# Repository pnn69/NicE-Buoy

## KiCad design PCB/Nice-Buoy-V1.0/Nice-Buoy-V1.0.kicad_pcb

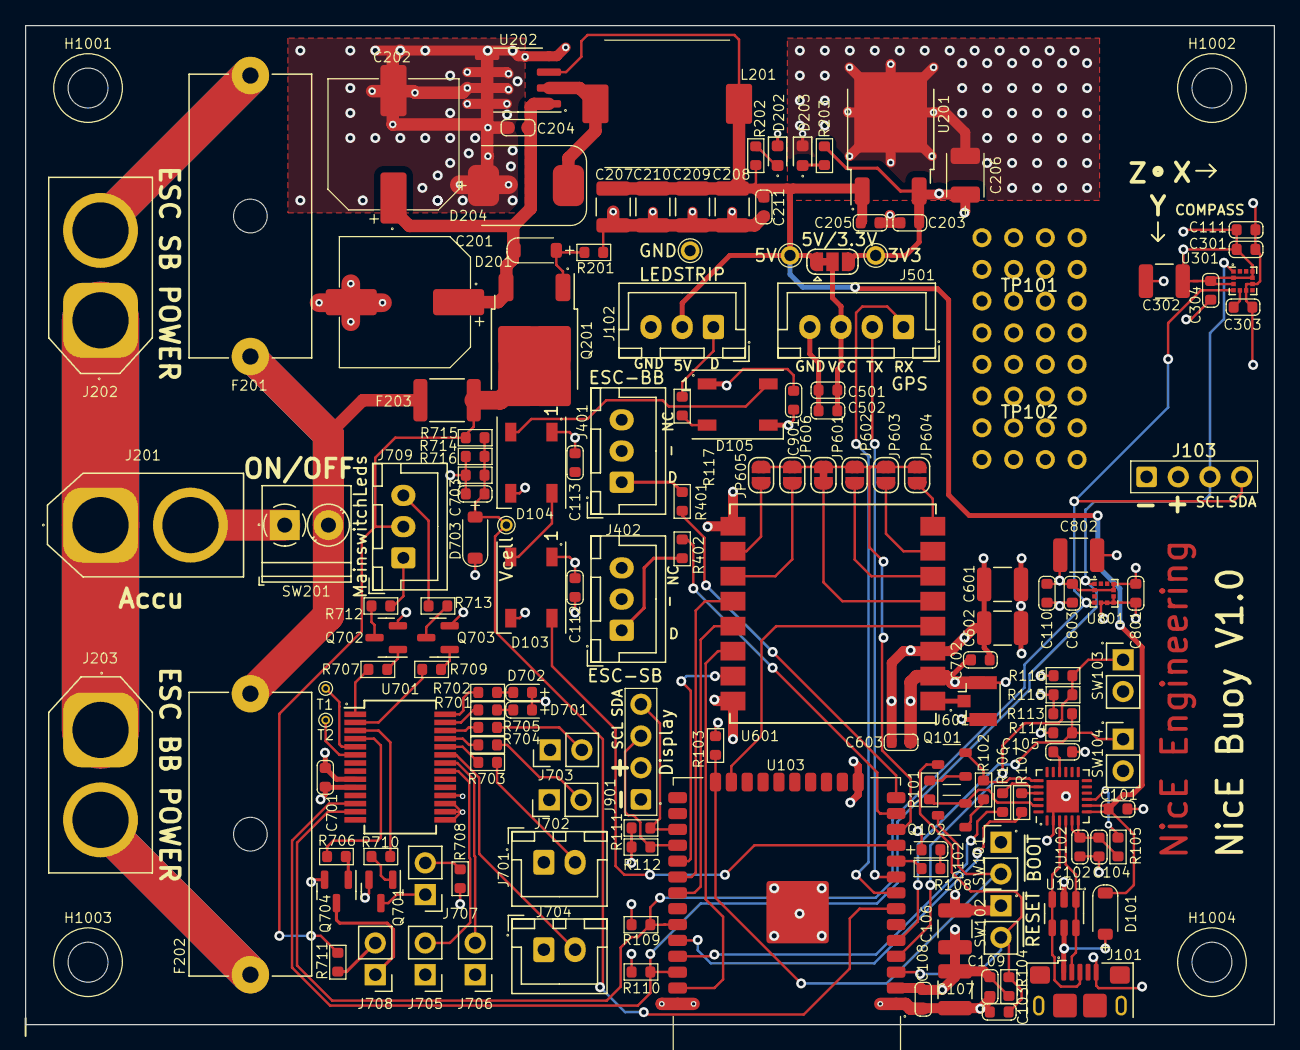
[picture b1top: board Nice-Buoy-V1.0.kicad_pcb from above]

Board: 4 copper layers, 100.0 x 80.0 mm, 154 parts (0 on the bottom side), 95 nets.

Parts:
C101, C102, C105: 4.7u; C_0603
C103, C104, C108, C109, C110, C111, C112, C113, C203, C204, C205, C211, C301, C303, C304, C501, C502, C603, C701, C702, C801, C803, C901: 100n; C_0603
C106, C107, C207, C208, C209, C210, C601, C602: 100u/16V; C_1210_3225Metric
C201, C202: 220u/50V; CP_ALU_D10x10.5
C206: 100u/6.3V; CP_TANT_3.5x2.8x1.9
C302, C802: 10u; C_1210_3225Metric
C703: 1n; C_0603
D101, D201, D703: SM4007PL; D_SOD-123_2.85x1.8x1.3
D102, D701: GREEN; LED_0603
D103, D104, D105: WS2812B; LED_WS2812B_PLCC4_5.0x5.0mm_P3.2mm
D202: 5V; LED_0603_1608Metric
D203: 3.3V; LED_0603_1608Metric
D204: SS36-E3/57T; D_SMC_7.1x6.2x2.65
D702: RED; LED_0603
F201, F202: 10A/T; Fuseholder_Cylinder-5x20mm_Schurter_0031_8201_Horizontal_Op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
F203: 3AT; Fuse_1812_4532Metric
H1001, H1002, H1003, H1004: MountingHole; NPTH_M3
J101: USB_B_Mini; USB_Micro-B_Amphenol_10118193-0001LF_Horizontal
J102: LEDSTRIP; JST_XH_B3B-XH-A_1x03_P2.50mm_Vertical
J103, J901: Display; Header_1x04_P2.54_Male
J201: Accu; AMASS_XT60-M_1x02_P7.20mm_Vertical
J202: ESC SB POWER; AMASS_XT60-F_1x02_P7.20mm_Vertical
J203: ESC BB POWER; AMASS_XT60-F_1x02_P7.20mm_Vertical
J401: ESC-BB; JST_XH_B3B-XH-A_1x03_P2.50mm_Vertical
J402: ESC-SB; JST_XH_B3B-XH-A_1x03_P2.50mm_Vertical
J501: GPS; JST_XH_B4B-XH-A_1x04_P2.50mm_Vertical
J601: Conn_Coaxial; U.FL_Hirose_U.FL-R-SMT-1_Vertical
J701: LED1; JST_XH_B2B-XH-A_1x02_P2.50mm_Vertical
J702: LED2; PinHeader_1x02_P2.54mm_Vertical
J703: LED3; PinHeader_1x02_P2.54mm_Vertical
J704: SW1; JST_XH_B2B-XH-A_1x02_P2.50mm_Vertical
J705: SW3; PinHeader_1x02_P2.54mm_Vertical
J706: SW2; PinHeader_1x02_P2.54mm_Vertical
J707: 3.3V switch; PinHeader_1x02_P2.54mm_Vertical
J708: Vbatt switch; PinHeader_1x02_P2.54mm_Vertical
J709: MainswitchLeds; JST_XH_B3B-XH-A_1x03_P2.50mm_Vertical
JP501: 5V/3.3V; SolderJumper-3_P1.3mm_Bridged12_RoundedPad1.0x1.5mm
JP601: D0; SolderJumper-2_P1.3mm_Bridged_RoundedPad1.0x1.5mm
JP602: D1; SolderJumper-2_P1.3mm_Open_RoundedPad1.0x1.5mm
JP603: D2; SolderJumper-2_P1.3mm_Open_RoundedPad1.0x1.5mm
JP604: D3; SolderJumper-2_P1.3mm_Open_RoundedPad1.0x1.5mm
JP605: D4; SolderJumper-2_P1.3mm_Open_RoundedPad1.0x1.5mm
JP606: D5; SolderJumper-2_P1.3mm_Open_RoundedPad1.0x1.5mm
L201: 68uH/3A; L_11.5x10.0mm
Q101, Q102: 2N7002; SOT-23_1.4x3_P0.95
Q201: NCE01P30K; TO-252-2
Q701, Q702, Q703, Q704: MMBT5551L; SOT-23
R101, R102, R103, R104, R105, R113, R114, R115, R116: 10K; R_0603
R106, R107: 120E; R_0603
R108, R203, R701, R702, R706, R707, R709, R710, R714, R716: 1k; R_0603
R109, R110, R111, R112: 2.2k; R_0603
R117, R201, R401, R402, R703, R704, R705, R708, R711: 100; R_0603
R202: 1.5k; R_0603
R712, R713: 4.7k; R_0603
R715: 6.2k; R_0603
SW101: ~{BOOT}; PinHeader_1x02_P2.54mm_Vertical
SW102: ~{RESET}; PinHeader_1x02_P2.54mm_Vertical
SW103: SW_SPST; PinHeader_1x02_P2.54mm_Vertical
SW104: SW2; PinHeader_1x02_P2.54mm_Vertical
SW201: ON/OFF; TerminalBlock_Phoenix_PT-1,5-2-3.5-H_1x02_P3.50mm_Horizontal
TP101: RW1; ReworkPins
TP102: RW2; ReworkPins
TP201: GND; Testpoint_0.9x1.5
TP202: 3V3; Testpoint_0.9x1.5
TP203: 5V; Testpoint_0.9x1.5
TP701: Vcell; Testpoint_0.6x1.0
TP702: T1; Testpoint_0.4x0.7
TP703: T2; Testpoint_0.4x0.7
U101: SRV05-4; SOT-23-6
U102: CP2104-F03-GMR; QFN-24-1EP_4x4mm_P0.5mm_EP2.6x2.6mm
U103: ESP32-WROOM-32E_(visible_peripherals); ESP32-WROOM-32
U201: AP7363; TO-252-2
U202: XL1509-5.0E1; SOIC-8_3.9x4.9mm_P1.27mm
U301: LSM303C; LGA-12_2x2mm_P0.5mm
U601: Ai-Thinker-Ra-01; Ai-Thinker-Ra-01-LoRa
U701: MCP23017_SS; SSOP-28_5.3x10.2mm_P0.65mm
U801: LIS2HH12; LGA-12_2x2mm_P0.5mm

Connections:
+3.3V: C106.1, C107.1, C108.1, C109.1, C110.1, C111.1, C112.1, C113.1, C205.1, C206.1, C301.1, C302.1, C304.1, C601.1, C602.1, C603.1, C701.1, C702.1, C801.1, C802.1, C803.1, C901.1, D102.2 (A), D103.1 (VDD), D104.1 (VDD), D105.1 (VDD), D701.2 (A), D702.2 (A), D703.1 (K), J103.2, J901.2, JP501.3 (B), R103.1, R104.1, R109.1, R110.1, R111.1, R112.1, R113.2, R115.2, R203.2, R708.1, TP202.1, U103.2 (VDD), U201.3 (VO), U301.2 (CS_XL), U301.3 (CS_MAG), U301.9 (VDD), U301.10 (VDDIO), U601.3 (VDD), U701.9 (VDD), U701.18 (~RESET), U801.2 (~CS), U801.9 (Vdd), U801.10 (Vdd_IO)
+5V: C101.2, C203.1, C207.1, C208.1, C209.1, C210.1, C211.1, D101.1 (K), J102.2, JP501.1 (A), L201.2, R202.1, TP203.1, U102.7 (REGIN), U102.8 (VBUS), U201.1 (VI), U202.3 (FB)
+28V: F203.2, J709.2, Q201.2 (D), R711.1, R715.1
/Accumonitor/GREEN: J709.1, R712.1
/Accumonitor/RED: J709.3, R713.2
/Accumonitor/Vbatt: C703.1, D703.2 (A), R714.1, R715.2, R716.1, TP701.1, U103.7 (GPIO35)
/CPU/ESC_BB: R401.1, U103.14 (MTDI/MISO/D2/GPIO12)
/CPU/ESC_SB: R402.1, U103.13 (MTMS/SCK/CLK/GPIO14)
/CPU/GPSRX: J501.1, U103.8 (GPIO32)
/CPU/GPSTX: J501.2, U103.9 (GPIO33)
/CPU/LEDS: D103.4 (DIN), U103.11 (GPIO26)
/CPU/RADIO_1: U103.37 (MOSI/GPIO23), U601.14 (MOSI)
/CPU/RADIO_2: U103.31 (MISO/GPIO19), U601.13 (MISO)
/CPU/RADIO_3: U103.30 (SCK/GPIO18), U601.12 (SCK)
/CPU/RADIO_4: U103.29 (CS/GPIO5), U601.15 (~NSS)
/CPU/RADIO_5: U103.23 (MTDO/CS/CMD/GPIO15), U601.4 (~RESET)
/CPU/RADIO_6: JP601.1 (A), JP602.1 (A), JP603.1 (A), JP604.1 (A), JP605.1 (A), JP606.1 (A), U103.12 (GPIO27)
/CPU/SCL: J103.3, R110.2, U103.36 (SCL/GPIO22), U301.1 (SCL/SPC), U701.12 (SCK), U801.1 (SCL/SPC)
/CPU/SCL_DISP: J901.3, R112.2, U103.28 (TXD/GPIO17)
/CPU/SDA: J103.4, R109.2, U103.33 (SDA/GPIO21), U301.4 (SDA/SDI/SDO), U701.13 (SDA), U801.4 (SDA/SDI)
/CPU/SDA_DISP: J901.4, R111.2, U103.27 (RXD/GPIO16)
/GPS/Vext: C501.1, C502.1, J501.3, JP501.2 (C)
/PSU/ACC: J201.2, SW201.1 (A)
/PSU/POWER: F201.2, F202.2, F203.1, SW201.2 (B)
DR0: Q102.3 (C), R103.2, SW101.2, U103.24 (D0/GPIO2)
DTR: Q102.2 (E), R101.2, U102.23 (DTR)
EN: C103.1, Q101.3 (C), R104.2, SW102.2, U103.3 (CHIP_PU/EN)
GND: C101.1, C102.1, C103.2, C104.1, C105.1, C106.2, C107.2, C108.2, C109.2, C110.2, C111.2, C112.2, C113.2, C201.2, C202.2, C203.2, C204.2, C205.2, C206.2, C207.2, C208.2, C209.2, C210.2, C211.2, C301.2, C302.2, C303.2, C304.2, C501.2, C502.2, C601.2, C602.2, C603.2, C701.2, C702.2, C703.2, C801.2, C802.2, C803.2, C901.2, D103.3 (VSS), D104.3 (VSS), D105.3 (VSS), D202.1 (K), D203.1 (K), D204.2 (A), J101.5 (GND), J102.3, J103.1, J201.1, J202.1, J203.1, J401.2, J402.2, J501.4, J601.2 (Ext), J701.1, J702.1, J703.1, J704.1, J705.1, J706.1, J901.1, Q701.2 (E), Q702.2 (E), Q703.2 (E), Q704.2 (E), R114.1, R116.1, R201.1, R714.2, R716.2, SW101.1, SW102.1, SW103.2 (B), SW104.2 (B), TP201.1, U101.2 (VN), U102.2 (GND), U102.25 (GND), U103.1 (GND), U103.15 (GND), U103.38 (GND), U103.39 (GND), U201.2 (GND), U202.4 (~EN), U202.5 (GND), U202.6 (GND), U202.7 (GND), U202.8 (GND), U301.6 (GND), U301.8 (GND), U601.2 (GND), U601.9 (GND), U601.16 (GND), U701.10 (VSS), U701.15 (A0), U701.16 (A1), U701.17 (A2), U801.5 (RES), U801.6 (GND), U801.7 (GND), U801.8 (GND)
LED1: R703.1, U701.24 (GPA3)
LED2: R704.1, U701.25 (GPA4)
LED3: R705.1, U701.26 (GPA5)
unnamed: D101.2 (A), J101.1 (VBUS), U101.5 (VP)
unnamed: D102.1 (K), R108.2
unnamed: D103.2 (DOUT), D104.4 (DIN)
unnamed: D104.2 (DOUT), D105.4 (DIN)
unnamed: D105.2 (DOUT), R117.2
unnamed: D201.2 (A), Q201.1 (G), R201.2
unnamed: C201.1, C202.1, C204.1, D201.1 (K), Q201.3 (S), U202.1 (VIN)
unnamed: D202.2 (A), R202.2
unnamed: D203.2 (A), R203.1
unnamed: D204.1 (K), L201.1, U202.2 (OUT)
unnamed: D701.1 (K), R701.2
unnamed: D702.1 (K), R702.2
unnamed: J101.3 (D+), U101.3 (IO2), U101.4 (IO3), U102.3 (D+)
unnamed: J101.2 (D-), U101.1 (IO1), U101.6 (IO4), U102.4 (D-)
unnamed: J102.1, R117.1
unnamed: F201.1, J202.2
unnamed: F202.1, J203.2
unnamed: J401.1, R401.2
unnamed: J402.1, R402.2
unnamed: J601.1 (In), U601.1 (ANT)
unnamed: J701.2, R703.2
unnamed: J702.2, R704.2
unnamed: J703.2, R705.2
unnamed: J707.1, Q701.3 (C)
unnamed: J707.2, R708.2
unnamed: J708.1, Q704.3 (C)
unnamed: J708.2, R711.2
unnamed: JP601.2 (B), U601.5 (DIO0)
unnamed: JP602.2 (B), U601.6 (DIO1)
unnamed: JP603.2 (B), U601.7 (DIO2)
unnamed: JP604.2 (B), U601.8 (DIO3)
unnamed: JP605.2 (B), U601.10 (DIO4)
unnamed: JP606.2 (B), U601.11 (DIO5)
unnamed: Q101.1 (B), R101.1
unnamed: Q102.1 (B), R102.1
unnamed: Q701.1 (B), R706.2
unnamed: Q702.1 (B), R707.2
unnamed: Q702.3 (C), R712.2
unnamed: Q703.1 (B), R709.2
unnamed: Q703.3 (C), R713.1
unnamed: Q704.1 (B), R710.2
unnamed: R115.1, R116.2, SW103.1 (A), U103.4 (GPIO36)
unnamed: R113.1, R114.2, SW104.1 (A), U103.5 (GPIO39)
unnamed: R106.2, U102.20 (RXD)
unnamed: R107.2, U102.21 (TXD)
unnamed: C102.2, C104.2, R105.1, U102.5 (VIO), U102.6 (VDD)
unnamed: C105.2, U102.16 (VPP)
unnamed: R105.2, U102.9 (~RSTb)
unnamed: R108.1, U103.10 (GPIO25)
unnamed: C303.1, U301.5 (C1)
unnamed: R701.1, U701.27 (GPA6)
unnamed: R702.1, U701.28 (GPA7)
unnamed: R707.1, U701.1 (GPB0)
unnamed: R709.1, U701.2 (GPB1)
unnamed: R706.1, U701.3 (GPB2)
unnamed: R710.1, U701.4 (GPB3)
unnamed: TP702.1, U701.5 (GPB4)
unnamed: TP703.1, U701.6 (GPB5)
RTS: Q101.2 (E), R102.2, U102.19 (RTS)
RX: R107.1, U103.34 (RXD/GPIO3)
SW1: J704.2, U701.23 (GPA2)
SW2: J706.2, U701.22 (GPA1)
SW3: J705.2, U701.21 (GPA0)
TX: R106.1, U103.35 (TXD/GPIO1)

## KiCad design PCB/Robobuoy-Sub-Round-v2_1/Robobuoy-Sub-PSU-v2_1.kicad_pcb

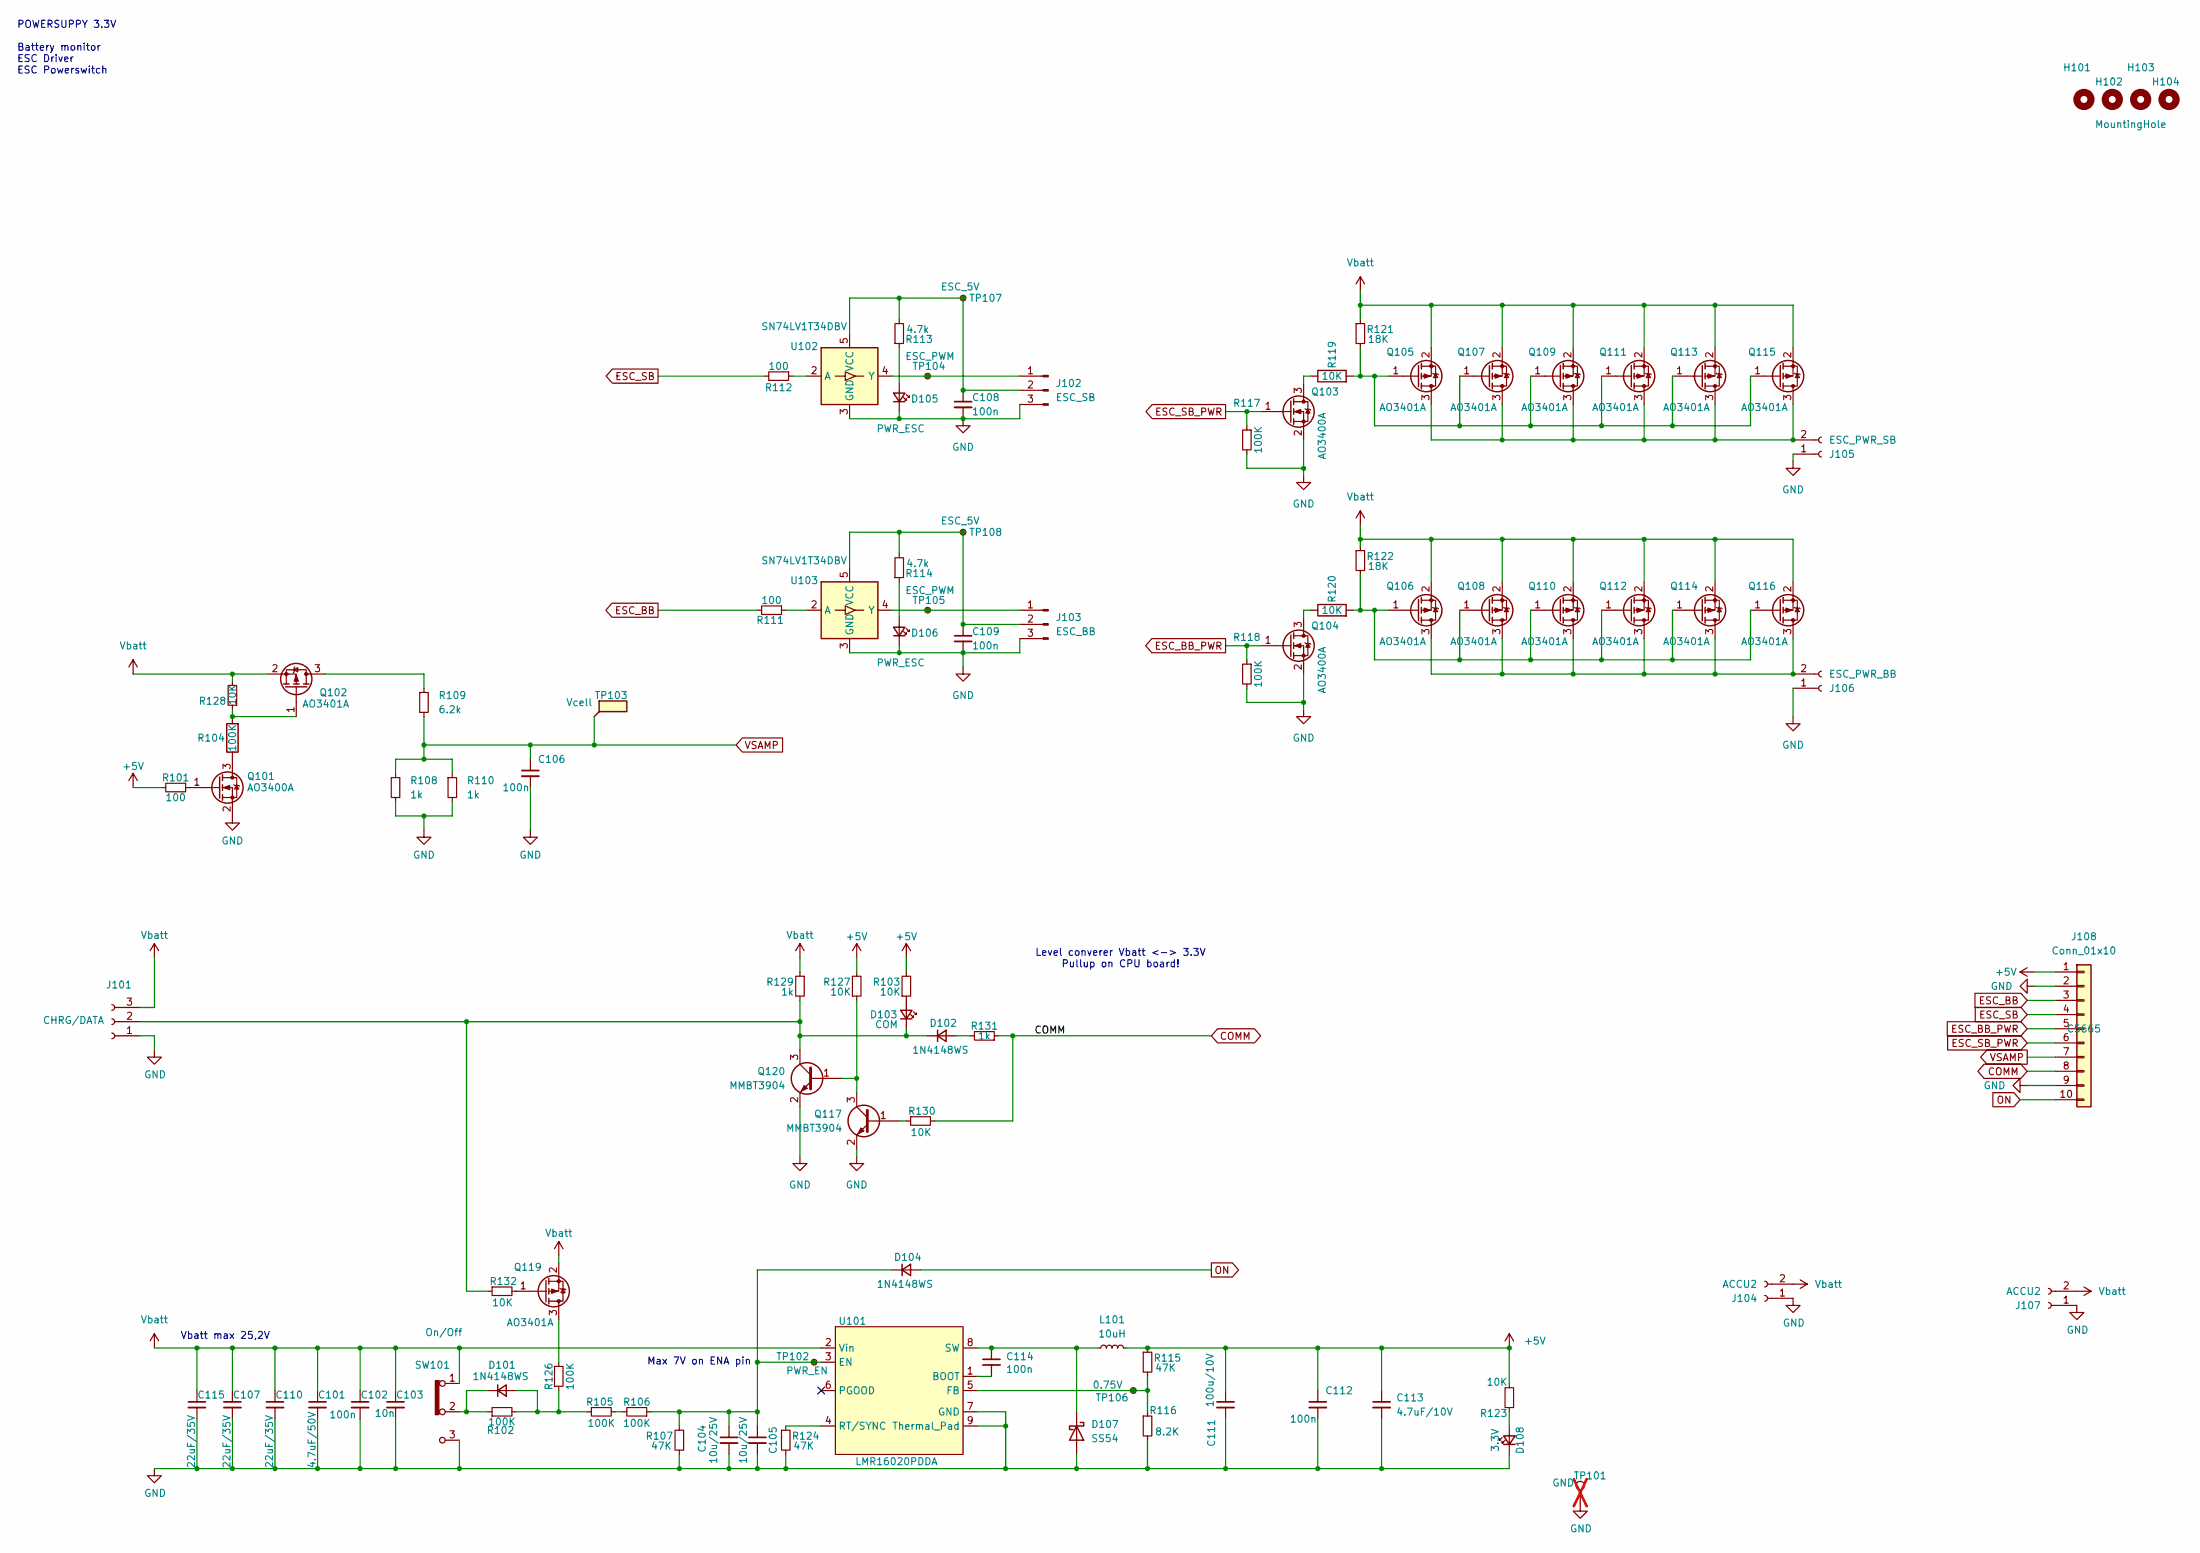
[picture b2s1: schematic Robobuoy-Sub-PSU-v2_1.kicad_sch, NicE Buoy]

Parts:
C101: 4.7uF/50V; C_1206_(1.6); LCSC C29823
C102, C106, C108, C109, C112, C114: 100n; C_0603; LCSC C14663
C103: 10n; C_0603; LCSC C57112
C104, C105: 10u/25V; C_0805; LCSC C15850
C107, C110, C115: 22uF/35V; C_1206_(1.6); LCSC C6119969
C111: 100u/10V; C_1210_3225Metric; LCSC C23742
C113: 4.7uF/10V; C_1206_(1.6); LCSC C29823
D101, D102, D104: 1N4148WS; D_SOD-323_1.8x1.4x1.15; LCSC C2128
D103: COM; LED_0603_1608Metric; LCSC C2286
D105, D106: PWR_ESC; LED_0603_1608Metric; LCSC C2286
D107: SS54; D_SMA; LCSC C22452
D108: 3.3V; LED_0805; LCSC C2297
H101, H102, H103, H104: MountingHole; NPTH_M3
J101: CHRG/DATA; MR60PW-M; LCSC C19268044
J102: ESC_SB; JST_XH_B3B-XH-A_1x03_P2.50mm_Vertical; LCSC C5341202
J103: ESC_BB; JST_XH_B3B-XH-A_1x03_P2.50mm_Vertical; LCSC C5341202
J104, J107: ACCU2; AMASS_XT60IPW-M_1x03_P7.20mm_Horizontal
J105: ESC_PWR_SB; AMASS_XT60PW-F_1x02_P7.20mm_Horizontal; LCSC C428722
J106: ESC_PWR_BB; AMASS_XT60PW-F_1x02_P7.20mm_Horizontal; LCSC C428722
J108: Conn_01x10; IDC-Header_2x05_P2.54mm_Vertical; LCSC C5665
L101: 10uH; L_6.6x7.0mm; LCSC C2894722
Q101, Q103, Q104: AO3400A; SOT-23; LCSC C20917
Q102, Q105, Q106, Q107, Q108, Q109, Q110, Q111, Q112, Q113, Q114, Q115, Q116, Q119: AO3401A; SOT-23; LCSC C15127
Q117, Q120: MMBT3904; SOT-23
R101, R111, R112: 100; R_0603; LCSC C22775
R102, R105, R106, R117, R118, R126: 100K; R_0603; LCSC C25804
R103, R123, R127, R128, R130, R132: 10K; R_0603; LCSC C25804
R104: 100K; R_0603; Farnell 2331736
R107, R115: 47K; R_0603
R108, R110, R129, R131: 1k; R_0603; LCSC C21190
R109: 6.2k; R_0603; LCSC C25804
R113, R114: 4.7k; R_0603; LCSC C4177
R116: 8.2K; R_0603
R119, R120: 10K; R_0603; Farnell 2331736
R121, R122: 18K; R_0603; LCSC C25810
R124: 47K; R_0603; LCSC C25819
SW101: On/Off; Header_1x03_P2.54_Male; LCSC C2937625
TP101: GND; TestPoint_Loop_D2.54mm_Drill1.5mm_Beaded; not fitted
TP102: PWR_EN; Testpad_1
TP103: Vcell; Testpad_1
TP104: ESC_PWM; Testpad_1
TP105: ESC_PWM; Testpad_1.4
TP106: 0.75V; Testpad_1
TP107, TP108: ESC_5V; Testpad_1
U101: LMR16020PDDA; SOIC-8-1EP_3.9x4.9mm_P1.27mm_EP2.41x3.81mm_ThermalVias; LCSC C190006
U102, U103: SN74LV1T34DBV; SOT-23-5; LCSC C100024

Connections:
+5V: C111.1, C112.1, C113.1, J108.1, L101.2, R101.2, R103.2, R115.1, R123.2, R127.2
COMM: J108.8, R130.2, R131.1
ESC_BB: J108.3, R111.2
ESC_BB_PWR: J108.5, Q104.1 (G), R118.1
ESC_SB: J108.4, R112.2
ESC_SB_PWR: J108.6, Q103.1 (G), R117.1
GND: C101.2, C102.2, C103.2, C104.2, C105.2, C106.2, C107.2, C108.2, C109.2, C110.2, C111.2, C112.2, C113.2, C115.2, D105.1 (K), D106.1 (K), D107.2 (A), D108.1 (K), J101.1, J102.3, J103.3, J104.1, J105.1, J106.1, J107.1, J108.2, J108.9, Q101.2 (S), Q103.2 (S), Q104.2 (S), Q117.2 (E), Q120.2 (E), R107.2, R108.2, R110.2, R116.2, R117.2, R118.2, R124.2, SW101.3, TP101.1, U101.7 (GND), U101.9 (Thermal_Pad), U102.3 (GND), U103.3 (GND)
unnamed: D101.2 (A), R102.2, R105.1, R126.1
unnamed: D101.1 (K), R102.1, SW101.2
unnamed: D102.2 (A), R131.2
unnamed: D102.1 (K), D103.1 (K), J101.2, Q120.3 (C), R129.2, R132.1
unnamed: D103.2 (A), R103.1
unnamed: C104.1, C105.1, D104.1 (K), R106.1, R107.1, TP102.1, U101.3 (EN)
unnamed: D105.2 (A), R113.1
unnamed: D106.2 (A), R114.1
unnamed: C114.1, D107.1 (K), L101.1, U101.8 (SW)
unnamed: D108.2 (A), R123.1
unnamed: J102.1, TP104.1, U102.4 (Y)
unnamed: C108.1, J102.2, R113.2, TP107.1, U102.5 (VCC)
unnamed: J103.1, TP105.1, U103.4 (Y)
unnamed: C109.1, J103.2, R114.2, TP108.1, U103.5 (VCC)
unnamed: J105.2, Q105.3 (D), Q107.3 (D), Q109.3 (D), Q111.3 (D), Q113.3 (D), Q115.3 (D)
unnamed: J106.2, Q106.3 (D), Q108.3 (D), Q110.3 (D), Q112.3 (D), Q114.3 (D), Q116.3 (D)
unnamed: Q101.3 (D), R104.1
unnamed: Q101.1 (G), R101.1
unnamed: Q102.3 (D), R109.1
unnamed: Q102.1 (G), R104.2, R128.1
unnamed: Q103.3 (D), R119.1
unnamed: Q104.3 (D), R120.1
unnamed: Q105.1 (G), Q107.1 (G), Q109.1 (G), Q111.1 (G), Q113.1 (G), Q115.1 (G), R119.2, R121.2
unnamed: Q106.1 (G), Q108.1 (G), Q110.1 (G), Q112.1 (G), Q114.1 (G), Q116.1 (G), R120.2, R122.2
unnamed: Q117.1 (B), R130.1
unnamed: Q117.3 (C), Q120.1 (B), R127.1
unnamed: Q119.3 (D), R126.2
unnamed: Q119.1 (G), R132.2
unnamed: R105.2, R106.2
unnamed: C114.2, U101.1 (BOOT)
unnamed: R115.2, R116.1, TP106.1, U101.5 (FB)
unnamed: R124.1, U101.4 (RT/SYNC)
unnamed: R112.1, U102.2 (A)
unnamed: R111.1, U103.2 (A)
ON: D104.2 (A), J108.10
VSAMP: C106.1, J108.7, R108.1, R109.2, R110.1, TP103.1
Vbatt: C101.1, C102.1, C103.1, C107.1, C110.1, C115.1, J101.3, J104.2, J107.2, Q102.2 (S), Q105.2 (S), Q106.2 (S), Q107.2 (S), Q108.2 (S), Q109.2 (S), Q110.2 (S), Q111.2 (S), Q112.2 (S), Q113.2 (S), Q114.2 (S), Q115.2 (S), Q116.2 (S), Q119.2 (S), R121.1, R122.1, R128.2, R129.1, SW101.1, U101.2 (Vin)

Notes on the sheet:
Max 7V on ENA pin
POWERSUPPY 3.3V Battery monitor ESC Driver ESC Powerswitch
Level converer Vbatt <-> 3.3V Pullup on CPU board!
Vbatt max 25,2V

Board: 4 copper layers, 98 parts (0 on the bottom side), 44 nets, no tracks yet.

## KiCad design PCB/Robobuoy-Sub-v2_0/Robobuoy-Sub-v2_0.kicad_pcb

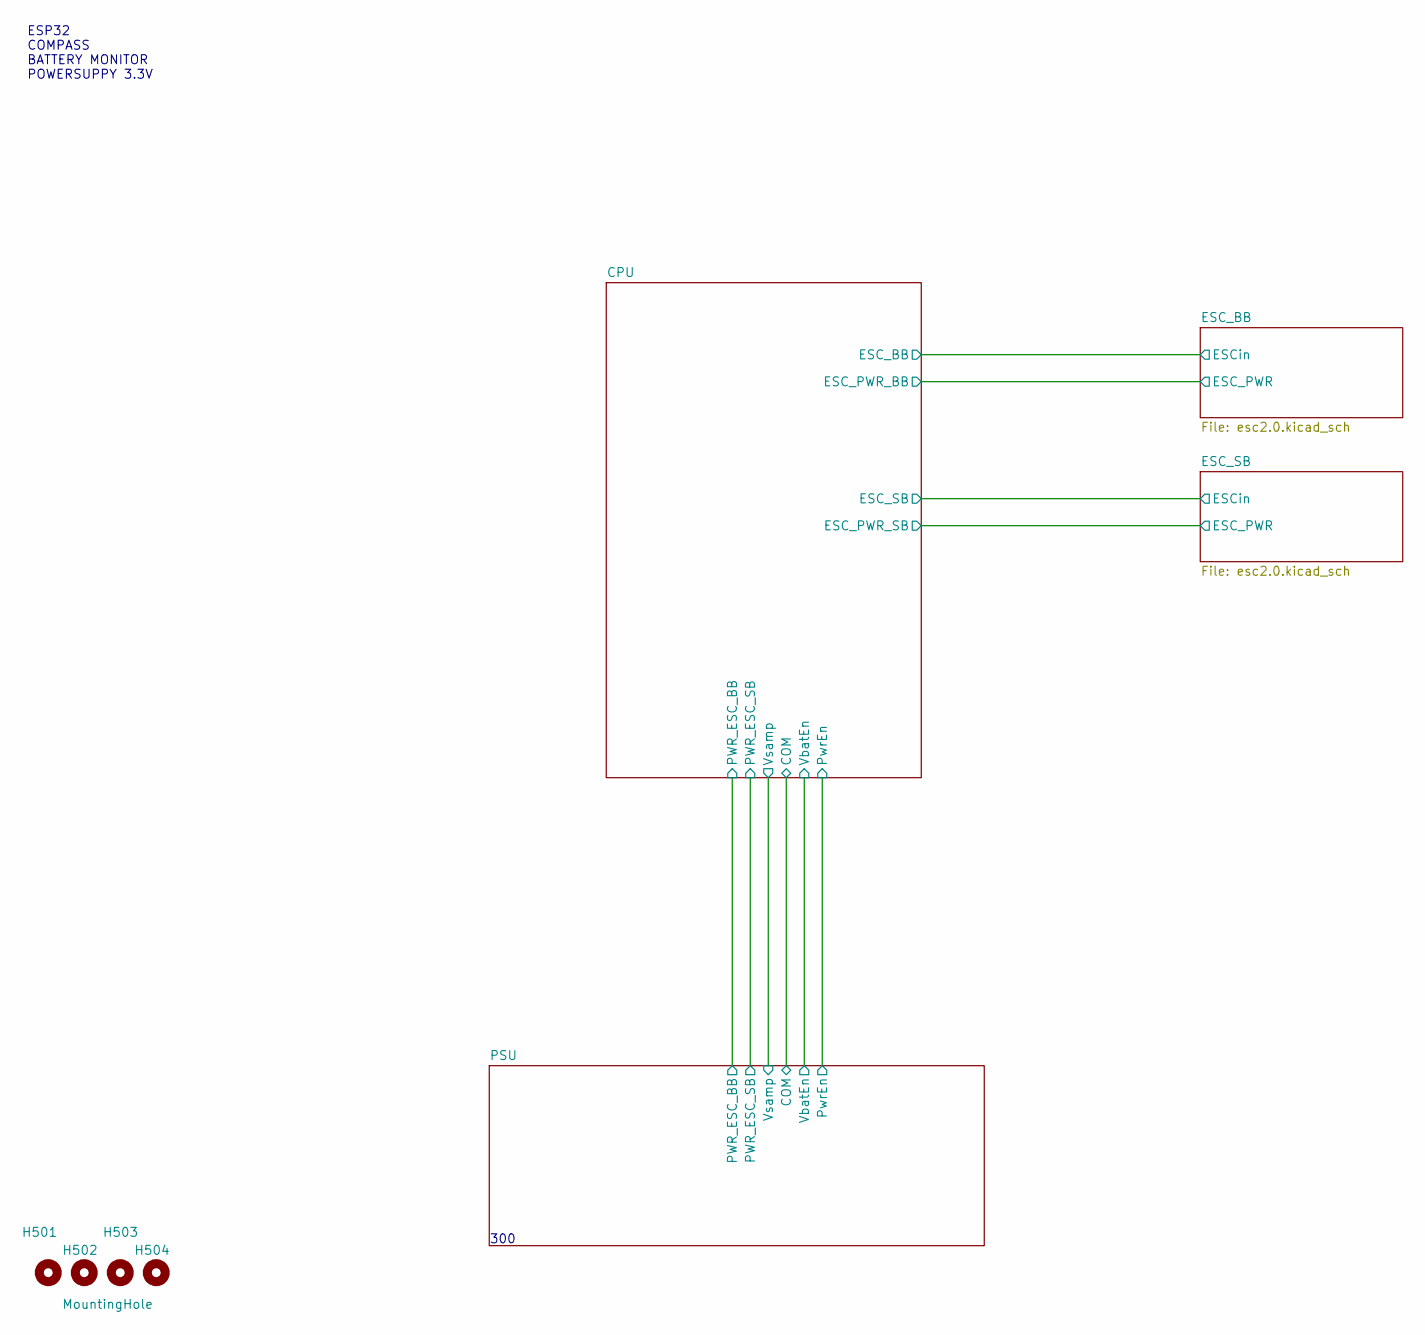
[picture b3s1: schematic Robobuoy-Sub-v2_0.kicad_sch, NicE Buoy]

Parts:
H501, H502, H503, H504: MountingHole; NPTH_M3

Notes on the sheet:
300
ESP32 COMPASS BATTERY MONITOR POWERSUPPY 3.3V

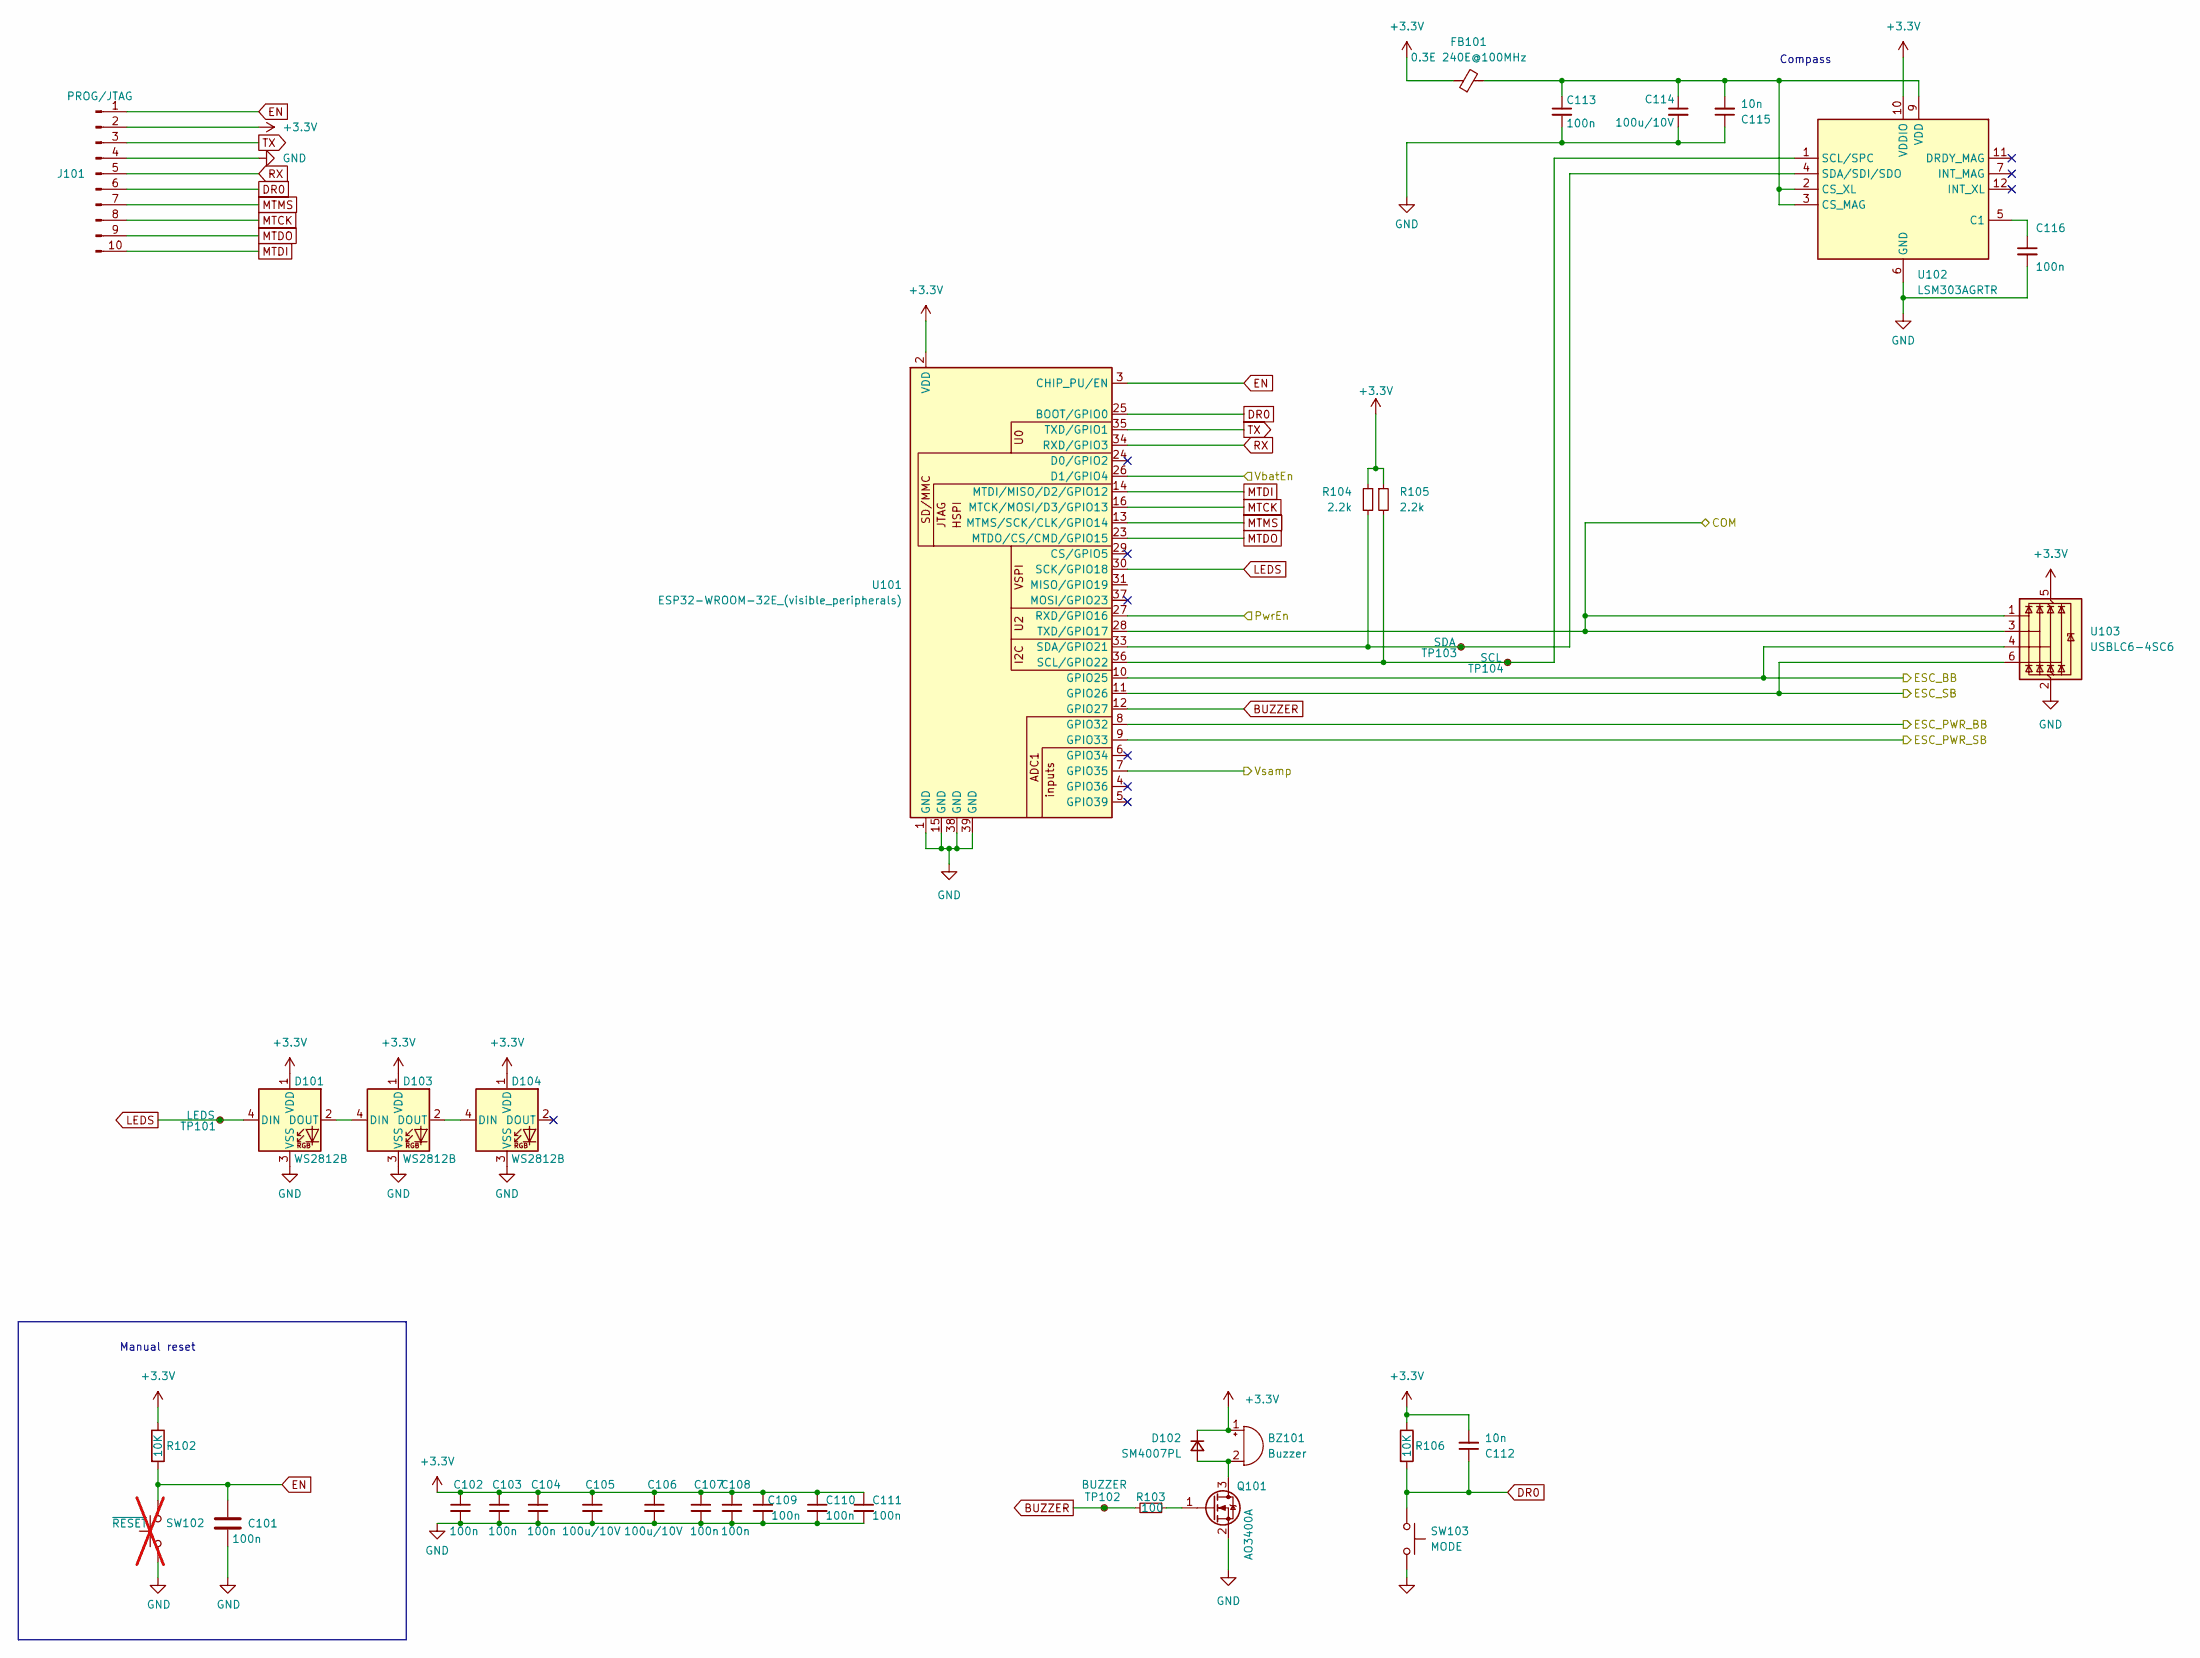
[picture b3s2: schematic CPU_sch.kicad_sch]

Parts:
BZ101: Buzzer; Buzzer-12x6.5x5.2; LCSC C968749
C101, C102, C103, C104, C107, C108, C109, C110, C111, C113, C116: 100n; C_0603; LCSC C14663
C105, C106, C114: 100u/10V; C_1210_3225Metric; LCSC C23742
C112, C115: 10n; C_0603; LCSC C57112
D101, D103, D104: WS2812B; LED_WS2812B_PLCC4_5.0x5.0mm_P3.2mm; LCSC C2843785
D102: SM4007PL; D_SOD-123_2.85x1.8x1.3; LCSC C64898
FB101: 0.3E 240E@100MHz; L_0805_(1.2); LCSC C2941558
J101: PROG/JTAG; IDC-Header_2x05_P2.54mm_Vertical; LCSC C5665
Q101: AO3400A; SOT-23; LCSC C20917
R102, R106: 10K; R_0603; Farnell 2331736
R103: 100; R_0603; LCSC C22775
R104, R105: 2.2k; R_0603; LCSC C4190
SW102: ~{RESET}; PinHeader_1x02_P2.54mm_Vertical; not fitted
SW103: MODE; SW_SPST_TL3342; LCSC C318884
TP101: LEDS; Testpad_1
TP102: BUZZER; Testpad_1
TP103: SDA; Testpad_1
TP104: SCL; Testpad_1
U101: ESP32-WROOM-32E_(visible_peripherals); ESP32-WROOM-32; LCSC C82899
U102: LSM303AGRTR; LGA-12_2x2mm_P0.5mm; LCSC C126671
U103: USBLC6-4SC6; SOT-23-6; LCSC C5197386

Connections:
+3.3V: BZ101.1 (+), C102.1, C103.1, C104.1, C105.1, C106.1, C107.1, C108.1, C109.1, C110.1, C111.1, C112.2, D101.1 (VDD), D102.1 (K), D103.1 (VDD), D104.1 (VDD), FB101.1, J101.2, R102.1, R104.1, R105.1, R106.1, U101.2 (VDD), U102.10 (VDDIO), U103.5 (VBUS); also elsewhere on the board
/CPU/COM: U101.28 (TXD/GPIO17), U103.1 (I/O1), U103.3 (I/O2); also elsewhere on the board
/CPU/ESC_BB: U101.10 (GPIO25), U103.4 (I/O3); also elsewhere on the board
/CPU/ESC_PWR_BB: U101.8 (GPIO32); also elsewhere on the board
/CPU/ESC_PWR_SB: U101.9 (GPIO33); also elsewhere on the board
/CPU/ESC_SB: U101.11 (GPIO26), U103.6 (I/O4); also elsewhere on the board
/CPU/PwrEn: U101.27 (RXD/GPIO16); also elsewhere on the board
/CPU/VbatEn: U101.26 (D1/GPIO4); also elsewhere on the board
/CPU/Vsamp: U101.7 (GPIO35); also elsewhere on the board
BUZZER: R103.2, TP102.1, U101.12 (GPIO27)
DR0: C112.1, J101.6, R106.2, SW103.2, U101.25 (BOOT/GPIO0)
EN: C101.1, J101.1, R102.2, SW102.2, U101.3 (CHIP_PU/EN)
GND: C101.2, C102.2, C103.2, C104.2, C105.2, C106.2, C107.2, C108.2, C109.2, C110.2, C111.2, C113.2, C114.2, C115.1, C116.2, D101.3 (VSS), D103.3 (VSS), D104.3 (VSS), J101.4, Q101.2 (S), SW102.1, SW103.1, U101.1 (GND), U101.15 (GND), U101.38 (GND), U101.39 (GND), U102.6 (GND), U102.8 (GND), U103.2 (GND); also elsewhere on the board
LEDS: D101.4 (DIN), TP101.1, U101.30 (SCK/GPIO18)
MTCK: J101.8, U101.16 (MTCK/MOSI/D3/GPIO13)
MTDI: J101.10, U101.14 (MTDI/MISO/D2/GPIO12)
MTDO: J101.9, U101.23 (MTDO/CS/CMD/GPIO15)
MTMS: J101.7, U101.13 (MTMS/SCK/CLK/GPIO14)
unnamed: BZ101.2 (-), D102.2 (A), Q101.3 (D)
unnamed: D101.2 (DOUT), D103.4 (DIN)
unnamed: D103.2 (DOUT), D104.4 (DIN)
unnamed: Q101.1 (G), R103.1
unnamed: R105.2, TP104.1, U101.36 (SCL/GPIO22), U102.1 (SCL/SPC)
unnamed: R104.2, TP103.1, U101.33 (SDA/GPIO21), U102.4 (SDA/SDI/SDO)
unnamed: C116.1, U102.5 (C1)
unnamed: C113.1, C114.1, C115.2, FB101.2, U102.2 (CS_XL), U102.3 (CS_MAG), U102.9 (VDD)
RX: J101.5, U101.34 (RXD/GPIO3)
TX: J101.3, U101.35 (TXD/GPIO1)

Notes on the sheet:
Compass
Manual reset

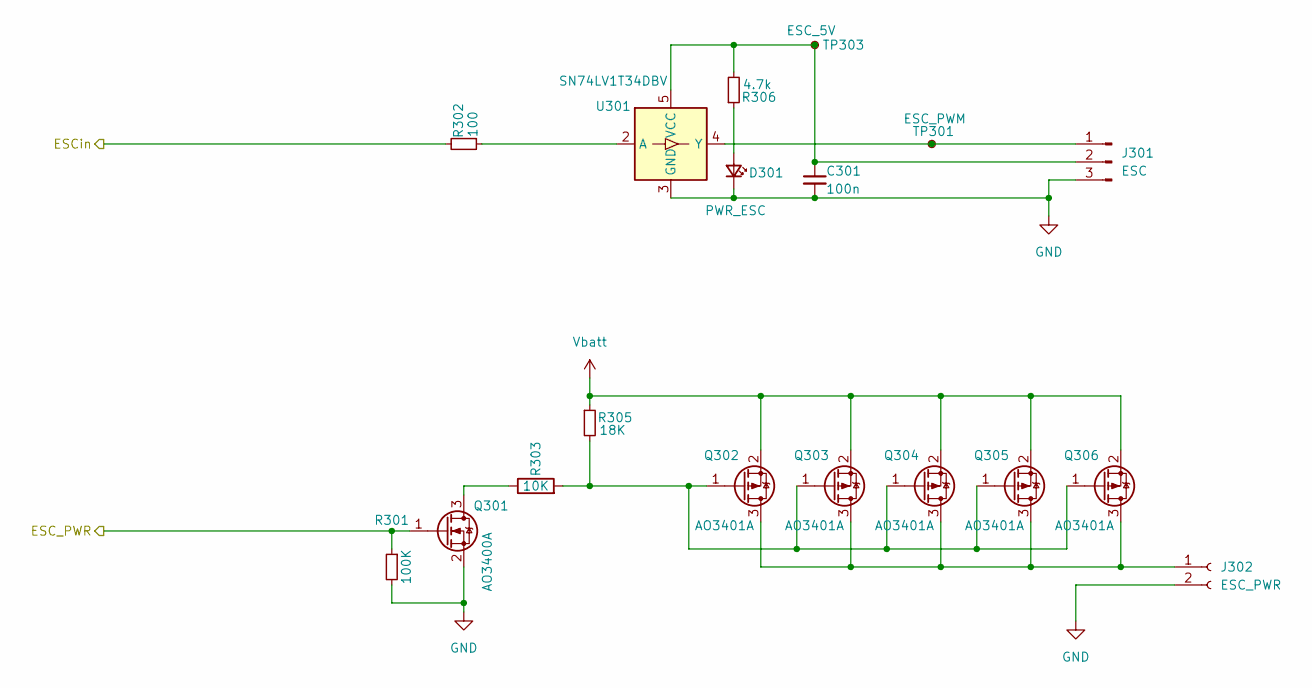
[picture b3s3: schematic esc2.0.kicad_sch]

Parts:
C301: 100n; C_0603; LCSC C14663
D301: PWR_ESC; LED_0603_1608Metric; LCSC C2286
J301: ESC; JST_XH_B3B-XH-A_1x03_P2.50mm_Vertical; LCSC C5341202
J302: ESC_PWR; SolderWire-0.75sqmm_1x02_P4.8mm_D1.25mm_OD2.3mm
Q301: AO3400A; SOT-23; LCSC C20917
Q302, Q303, Q304, Q305, Q306: AO3401A; SOT-23; LCSC C15127
R301: 100K; R_0603; LCSC C25804
R302: 100; R_0603; LCSC C22775
R303: 10K; R_0603; Farnell 2331736
R305: 18K; R_0603; LCSC C25810
R306: 4.7k; R_0603; LCSC C4177
TP301: ESC_PWM; Testpad_1
TP303: ESC_5V; Testpad_1
U301: SN74LV1T34DBV; SOT-23-5; LCSC C100024

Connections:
/CPU/ESC_PWR_SB: Q301.1 (G), R301.1; also elsewhere on the board
/CPU/ESC_SB: R302.2; also elsewhere on the board
GND: C301.2, D301.1 (K), J301.3, J302.2, Q301.2 (S), R301.2, U301.3 (GND); also elsewhere on the board
unnamed: D301.2 (A), R306.1
unnamed: J301.1, TP301.1, U301.4 (Y)
unnamed: C301.1, J301.2, R306.2, TP303.1, U301.5 (VCC)
unnamed: J302.1, Q302.3 (D), Q303.3 (D), Q304.3 (D), Q305.3 (D), Q306.3 (D)
unnamed: Q301.3 (D), R303.1
unnamed: Q302.1 (G), Q303.1 (G), Q304.1 (G), Q305.1 (G), Q306.1 (G), R303.2, R305.2
unnamed: R302.1, U301.2 (A)
Vbatt: Q302.2 (S), Q303.2 (S), Q304.2 (S), Q305.2 (S), Q306.2 (S), R305.1; also elsewhere on the board

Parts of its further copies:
C401: 100n; C_0603; LCSC C14663
D401: PWR_ESC; LED_0603_1608Metric; LCSC C2286
J401: ESC; JST_XH_B3B-XH-A_1x03_P2.50mm_Vertical; LCSC C5341202
J402: ESC_PWR; SolderWire-0.75sqmm_1x02_P4.8mm_D1.25mm_OD2.3mm
Q401: AO3400A; SOT-23; LCSC C20917
Q402, Q403, Q404, Q405, Q406: AO3401A; SOT-23; LCSC C15127
R401: 100K; R_0603; LCSC C25804
R402: 100; R_0603; LCSC C22775
R403: 10K; R_0603; Farnell 2331736
R405: 18K; R_0603; LCSC C25810
R406: 4.7k; R_0603; LCSC C4177
TP401: ESC_PWM; Testpad_1
TP403: ESC_5V; Testpad_1
U401: SN74LV1T34DBV; SOT-23-5; LCSC C100024

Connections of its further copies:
/CPU/ESC_BB: R402.2; also elsewhere on the board
/CPU/ESC_PWR_BB: Q401.1 (G), R401.1; also elsewhere on the board
GND: C401.2, D401.1 (K), J401.3, J402.2, Q401.2 (S), R401.2, U401.3 (GND); also elsewhere on the board
unnamed: D401.2 (A), R406.1
unnamed: J401.1, TP401.1, U401.4 (Y)
unnamed: C401.1, J401.2, R406.2, TP403.1, U401.5 (VCC)
unnamed: J402.1, Q402.3 (D), Q403.3 (D), Q404.3 (D), Q405.3 (D), Q406.3 (D)
unnamed: Q401.3 (D), R403.1
unnamed: Q402.1 (G), Q403.1 (G), Q404.1 (G), Q405.1 (G), Q406.1 (G), R403.2, R405.2
unnamed: R402.1, U401.2 (A)
Vbatt: Q402.2 (S), Q403.2 (S), Q404.2 (S), Q405.2 (S), Q406.2 (S), R405.1; also elsewhere on the board
